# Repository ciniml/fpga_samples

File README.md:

# FPGA Samples

GOWIN LittleBeeなどの小規模FPGA向けのサンプルやライブラリ

## 内容

### rtl

SystemVerilogで記述したモジュール

### src/main/scala

Chisel3で記述したモジュール

### src/test/scala

Chisel3で記述したモジュールのテスト

## ライセンス

Boost Software License 1.0

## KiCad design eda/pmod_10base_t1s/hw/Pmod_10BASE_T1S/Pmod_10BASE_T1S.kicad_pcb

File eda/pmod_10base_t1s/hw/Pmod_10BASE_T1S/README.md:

# Pmod 10BASE-T1S (Rev. A)

IEEE 802.3cg 10BASE-T1S のバスに、**PHY チップを使わずに**つなぐ Pmod 基板。PCS / PMA / PLCA は FPGA のロジック
(`rtl/t1s_phy`) で実装し、基板には受動部品と、アナログスイッチ 1 個・CMC・ESD アレイだけを載せる。
送信は「RC + アナログスイッチ」と「直列インダクタ (Basic / Preferred 部品だけ)」の 2 通りを載せてあり、ハンダジャンパで選ぶ。
検討の経緯と規格の要件は [`../../README.md`](../../README.md)。KiCad 10、2 層。

状態: **設計のみ (未発注・実機未確認)**。

## 仕様

- 外形 20.32 × 44 mm (Pmod 1 スロット幅)、2 層 1.6 mm (B.Cu は GND ベタ)、角 1.27 mm 面取り。
- J1: Pmod 2x6 直角ヘッダ (`Conn_Pmod_Spec_B_Thin`)、上端。Digilent のピン 1 は部品面から見て右端。
- J2: 5.0 mm 2 ピンねじ端子 (KF301-5.0-2P、フットプリントは互換の MaiXu MX126)、下端。1 = BI_DA+ (シルク「+」)、2 = BI_DA−。
  DME は極性に依存しないので逆につないでも動く。挿入実装なので手はんだを既定にする (`jlc_files.py --with-tht` で JLC 実装に含める)。
- J3: 2.54 mm 3 ピン (線 +、線 −、GND、**未実装**)。プローブやジャンパ線用。
- JP1: 2 ピンヘッダ + ショートピン。**バスの両端のノードだけ**挿して 100 Ω のエンド終端を入れる。
- JP2 / JP3: 3 パッドのハンダジャンパ (TX+ / TX−)。送信経路の選択 (下の「送信経路の切り替え」)。
- 電源: Pmod VCC (3.3 V) のみ。PoDL 非対応 (給電されたバスにつながない)。

| J1 ピン | 信号 | 種類 | TP25K J6 (pmod0) |
|---|---|---|---|
| 1 / 7 | CMP_HP / CMP_HN (比較器 H: v > +th) | LVDS25 入力 | F5 / G5 |
| 2 / 8 | CMP_LP / CMP_LN (比較器 L: v > −th) | LVDS25 入力 | G7 / G8 |
| 3 | PWM_TH (しきい値) | LVCMOS33 出力 | H8 |
| 9 | TX_EN (TMUX1511 SEL1/SEL2、基板で 10 kΩ プルダウン。L 経路では常に Low) | LVCMOS33 出力 | H7 |
| 4 / 10 | TX_P / TX_N | LVCMOS33 出力 DRIVE=16 | H5 / J5 |

並びは `eda/pmod_100base_tx` と同じ (9 番だけ 2 本目の PWM から TX_EN に変更)。

## 回路

| Ref | 値 | 役割 |
|---|---|---|
| R1 / R2 | 100 Ω | 送信の直列抵抗 (FPGA 側、両経路で共通)。SW 経路はピン抵抗 + R1 + Ron + R5 ≈ 145 Ω/片側で、50 Ω (両端終端の並列) に約 1.0 Vpp。実測で合わせる |
| JP2 / JP3 | ハンダジャンパ 3 パッド | 中央 = R1 / R2 の出力。1-2 (出荷時、銅箔で短絡) = SW 経路、2-3 = L 経路 |
| C1 / C2 | 220 pF | SW 経路: 立ち上がりを約 10 ns (20〜80%) に鈍らせる。スイッチの FPGA 側にあるので、休止中はバスから見えない |
| U1 | TMUX1511 | SW 経路: 送信の切り離し (SW1/SW2、SEL = TX_EN)。Ron 2 Ω、COFF 最大 4 pF、電源断でも 3.6 V まで絶縁。SW3/SW4 は未使用 (GND) |
| R5 / R6 | 22 Ω | SW 経路: 送信の直列抵抗 (線路側) |
| L2 / L3 | 1 µH 0805 (Sunlord SDFL2012Q1R0KTF、50 mA) | L 経路: R1 / R2 と直列で立ち上がりを鈍らせ、TRX に直結。直列素子なので休止中に容量として見えない |
| R7 | 10 kΩ | TX_EN のプルダウン (FPGA の未コンフィグ時の弱プルアップでスイッチが入らないように) |
| R8 / R9 | 20 kΩ | TRX_P / TRX_N を VB にバイアス (比較器の VB 側の入力を兼ねる) |
| C4 / C5、R12 / R14 | 100 nF、20 kΩ | 比較器の VTH 側のタップ (AC 結合 + VTH へバイアス) |
| R10 / R11 / R13 / R15 | 1 kΩ | FPGA の各ピンとの直列抵抗 (ピン容量を高域で隠す、ESD 電流の制限) |
| R16 / R17 / C6 / C7 | 3.3 kΩ / 2 kΩ / 10 µF / 100 nF | VB = 1.245 V |
| R18 / R19 / C8 | 5.1 kΩ / 1 kΩ / 1 µF | PWM → VTH。th = VTH − VB = (D × 3.3 V − VB) × 0.164 = −204〜+337 mV |
| U2 | TPD4E02B04 | ESD (トランシーバ側、2 チャネル使用、フロースルー) |
| L1 | ACT1210L-201 (200 µH) | コモンモードチョーク。フットプリントはデータシートの推奨ランドから生成 (`gen_sch.py`) |
| C9 / C10 | 100 nF 50 V | DC 阻止 |
| R20 / R21 / C11 / R22 | 49.9 Ω ×2 / 100 nF / 100 kΩ | エンド終端 (JP1 で入/切) と静電気逃がし (OPEN Alliance の R1/R2/C3/R3) |
| R23 / R24 | 1.5 kΩ (**未実装**) | コモンモード終端 (ドロップノードの任意項目) |
| C12 / C13 / C3 | 10 µF / 100 nF / 100 nF | 3.3 V、U1 の電源 |

## 送信経路の切り替え

| | SW 経路 (JP2 / JP3 = 1-2、出荷時) | L 経路 (JP2 / JP3 = 2-3) |
|---|---|---|
| 回路 | 100 Ω → 220 pF → TMUX1511 → 22 Ω | 100 Ω → 1 µH → TRX 直結 |
| 振幅 (50 Ω) | 約 1.0 Vpp | 1.00〜1.13 Vpp (FPGA のピン抵抗 40〜20 Ω) |
| 立ち上がり (20〜80%、50 Ω‖15 pF) | 約 10 ns | 10.5〜11.8 ns |
| 休止中の high-Z | スイッチで切断 (電源断でも) | FPGA のトライステート。電源断時は DC 阻止の後ろで ±0.25 V しか振れないので FPGA の保護ダイオードはほぼ導通しない |
| 休止中の容量 | TMUX の COFF + 22 Ω | FPGA の TX ピン容量 (推定 5〜10 pF) を 100 Ω + 1 µH 越しに見る。5 pF なら全帯域で下限を満たす (40 MHz で 202 Ω、下限 159 Ω)。10 pF だと直列共振が 50 MHz に下がり、40 MHz で 152 Ω と下限をわずかに割る (`../../tools/calc.py`、要実測) |
| Extended 部品 | TMUX1511 | なし (L2 / L3 は Preferred) |
| FPGA の設定 | `d` = 0 (既定): TX_EN でスイッチ、TX ピンは常に駆動 | `d` = 1: TX_EN は常に Low、TX ピンは P ≠ N の間だけ駆動 (アイドルと PRE / POST はトライステート) |

- 切り替え: 1-2 の間の細い銅箔をカッターで切り、2-3 をハンダでつなぐ。戻すときは 2-3 のハンダを除いて 1-2 をつなぐ。
  L 経路では U1 は載っていてもよい (TX_EN が Low なのでオフ)。
- **発注は両方の経路を載せる構成を既定とする** (`fab/jlc` の BOM / CPL は U1・C1〜C3・R5 / R6 と L2 / L3 をすべて含む)。ジャンパだけで 2 方式を
  実測で比べられるため (TMUX1511 の LCSC 単体の在庫は 2026-11-20 に 0、11-21 に 1,863 個と変動する)。
  コスト (2026-11-21、JLC 少量単価、Extended 手数料 $3/種類): 両方載せると 5 枚で約 $17.1 (部品 $1.62/枚 + 手数料 $9)。
  SW 経路だけなら $16.6、L 経路だけ (U1 / C1〜C3 / R5 / R6 なし) なら $11.4 で、L 経路だけにして減るのは U1 の手数料 $3 と部品 約 $0.43/枚。
  大きく効くのは U2 (ESD) と L1 (CMC) で、手数料 $6 と部品 $0.89/枚 (ただし線路の保護をなくすことになる。L1 を外すには迂回パッドの追加が要る)。
- **SW 経路のまま L2 / L3 が載っていても問題ない** (ジャンパの 3 番が開いているので L は片側が浮く)。逆に L 経路で 1-2 の銅箔を
  切り忘れると、220 pF が L 越しにバスに見えて休止中の容量が規格を大きく超える。
- L 経路の値は ngspice の見積り (`tools/tx_lr.cir`)。FPGA の DRIVE 設定でピン抵抗が変わるので、振幅はオシロで確認する。

## 配線

- 自動配線 (circuitpnr、F.Cu / B.Cu)。ESD アレイの対向パッド (フロースルー) から CMC、CMC から DC 阻止コンデンサまでは
  `tools/gen_pcb.py` で手引き (自動配線が対向パッドの片側を取りこぼすため)。
- 12.5 MBd なので等長・差動インピーダンスは考慮していない。線路系のネット (LINE_*, CM_*, TRX_*) は幅 0.3 mm。

## 生成と製造データ

`tools/build.sh --regen` で回路図・基板を作り直し (gen_sch.py → gen_pcb.py → circuitpnr route / labels)、ERC / DRC
(回路図との一致を含む) のあと `fab/` にガーバー、ドリル、BOM、配置、回路図 PDF、画像を書く。`--regen` なしは今の KiCad ファイルから
製造データだけを出す。生成の流儀は Pmod_DVI / Pmod_GbE と同じ (Python)。

部品 (2026-11-20 照会): TMUX1511PWR は JLC 実装在庫 7,737 個 (LCSC 単体の在庫は 0、11-21 の再照会で 1,863 個)、ACT1210L-201 は 2.6 万個、TPD4E02B04 は 7.2 万個。
2026-11-21 照会: 抵抗は全部 Basic (22 Ω C25092、3.3 kΩ C25890、2 kΩ C4109、5.1 kΩ C25905 に変更)、1 µH の C1042 は Preferred (在庫 6 万個)。
Extended は U1 (TMUX1511)・U2 (ESD)・L1 (CMC)・J2 (ねじ端子、既定で手はんだ) の 4 種類。
`tools/lcsc_order.py N` で手はんだ用の LCSC 購入リスト (`fab/lcsc/`、5 枚分を 2026-11-21 に再生成。C14663 (100 nF 50 V 0603) と C1042 (1 µH) は LCSC 単体の在庫が 0 なので、手はんだ分は同等品を探す)。

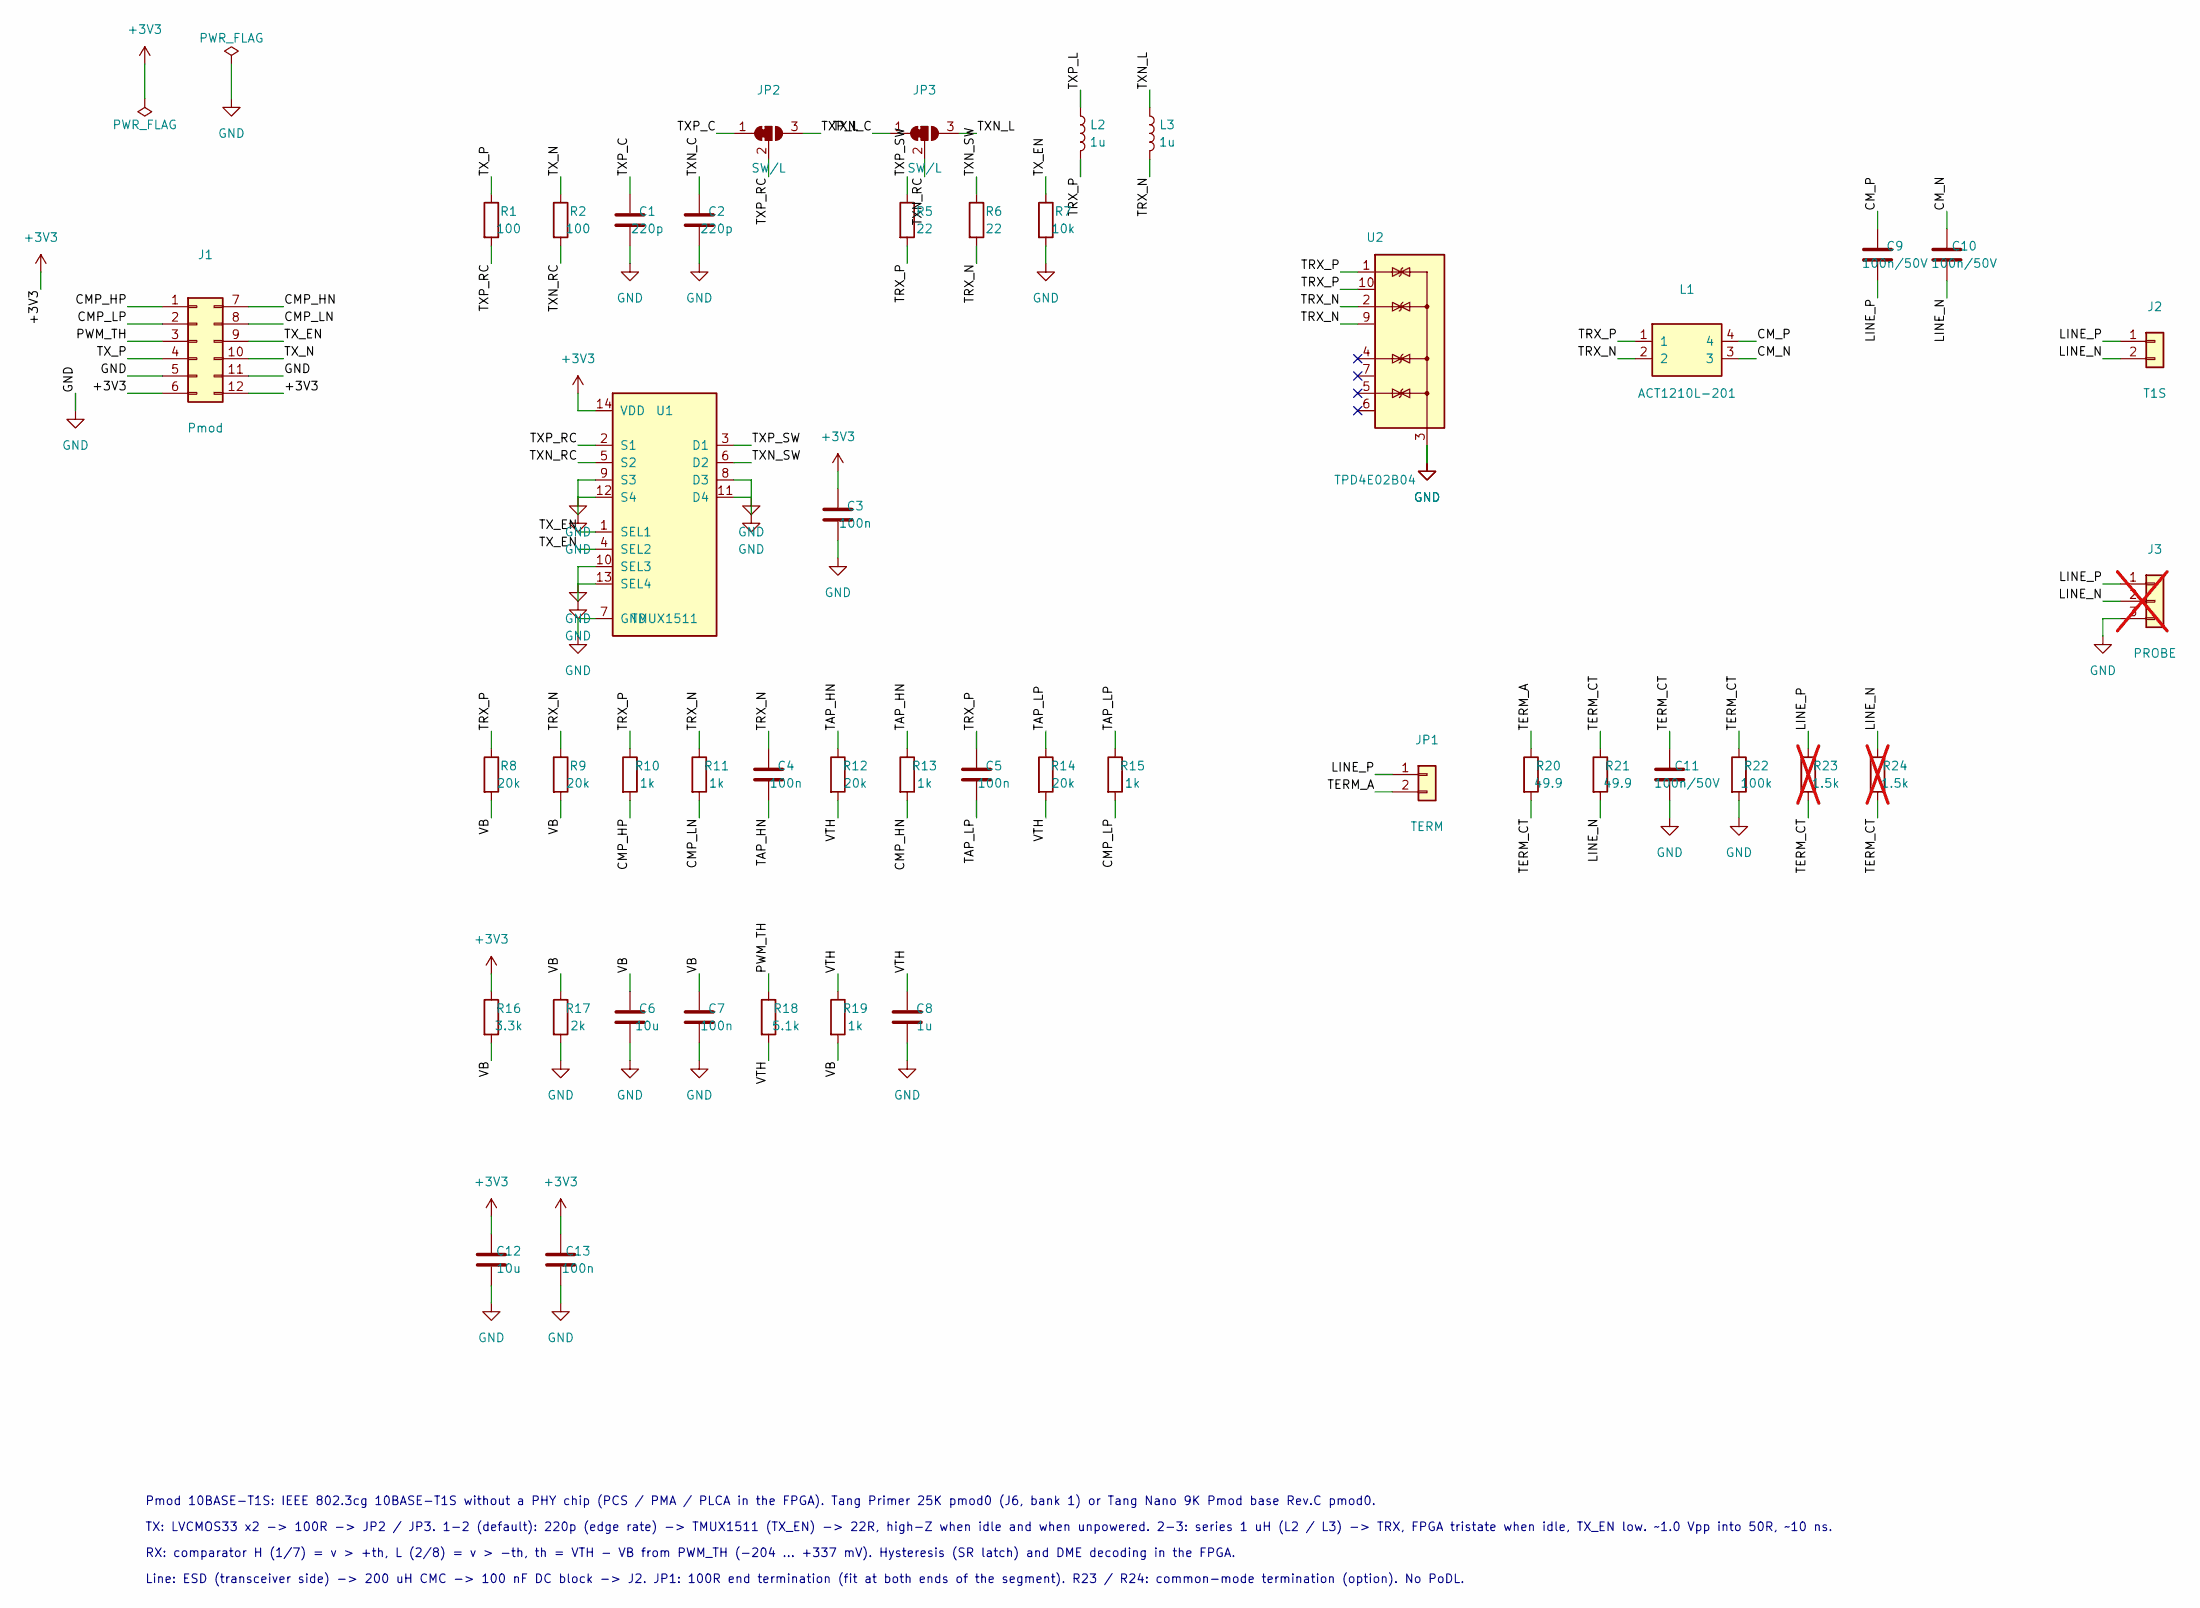
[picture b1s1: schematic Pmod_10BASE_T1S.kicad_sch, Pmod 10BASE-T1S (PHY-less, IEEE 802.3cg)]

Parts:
C1, C2: 220p; C_0402_1005Metric; MPN FH 0402B221K500NT; LCSC C1530
C3, C4, C5, C7, C13: 100n; C_0402_1005Metric; MPN Samsung CL05B104KO5NNNC; LCSC C1525
C6, C12: 10u; C_0603_1608Metric; MPN Samsung CL10A106KP8NNNC; LCSC C19702
C8: 1u; C_0402_1005Metric; MPN Samsung CL05A105KA5NQNC; LCSC C52923
C9, C10, C11: 100n/50V; C_0603_1608Metric; MPN YAGEO CC0603KRX7R9BB104; LCSC C14663
J1: Pmod; Conn_Pmod_Spec_B_Thin
J2: T1S; TerminalBlock_MaiXu_MX126-5.0-02P_1x02_P5.00mm; MPN Cixi Kefa KF301-5.0-2P; LCSC C474881
J3: PROBE; PinHeader_1x03_P2.54mm_Vertical; not fitted
JP1: TERM; PinHeader_1x02_P2.54mm_Vertical
JP2, JP3: SW/L; SolderJumper-3_P1.3mm_Bridged12_RoundedPad1.0x1.5mm_NumberL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
L1: ACT1210L-201; L_CommonModeChoke_TDK_ACT1210; MPN TDK ACT1210L-201-2P-TL00; LCSC C131444
L2, L3: 1u; L_0805_2012Metric; MPN Sunlord SDFL2012Q1R0KTF; LCSC C1042
R1, R2: 100; R_0402_1005Metric; MPN UNI-ROYAL 0402WGF1000TCE; LCSC C25076
R5, R6: 22; R_0402_1005Metric; MPN UNI-ROYAL 0402WGF220JTCE; LCSC C25092
R7: 10k; R_0402_1005Metric; MPN UNI-ROYAL 0402WGF1002TCE; LCSC C25744
R8, R9, R12, R14: 20k; R_0402_1005Metric; MPN UNI-ROYAL 0402WGF2002TCE; LCSC C25765
R10, R11, R13, R15, R19: 1k; R_0402_1005Metric; MPN UNI-ROYAL 0402WGF1001TCE; LCSC C11702
R16: 3.3k; R_0402_1005Metric; MPN UNI-ROYAL 0402WGF3301TCE; LCSC C25890
R17: 2k; R_0402_1005Metric; MPN UNI-ROYAL 0402WGF2001TCE; LCSC C4109
R18: 5.1k; R_0402_1005Metric; MPN UNI-ROYAL 0402WGF5101TCE; LCSC C25905
R20, R21: 49.9; R_0402_1005Metric; MPN UNI-ROYAL 0402WGF499JTCE; LCSC C25120
R22: 100k; R_0402_1005Metric; MPN UNI-ROYAL 0402WGF1003TCE; LCSC C25741
R23, R24: 1.5k; R_0603_1608Metric; MPN UNI-ROYAL 0603WAF1501T5E; LCSC C22843; not fitted
U1: TMUX1511; TSSOP-14_4.4x5mm_P0.65mm; MPN TI TMUX1511PWR; LCSC C2866750
U2: TPD4E02B04; USON-10_2.5x1.0mm_P0.5mm; MPN TI TPD4E02B04DQAR; LCSC C106794

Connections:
+3V3: C3.1, C12.1, C13.1, J1.6, J1.12, R16.1, U1.14 (VDD)
/CMP_HN: J1.7, R13.2
/CMP_HP: J1.1, R10.2
/CMP_LN: J1.8, R11.2
/CMP_LP: J1.2, R15.2
/CM_N: C10.1, L1.3
/CM_P: C9.1, L1.4
/LINE_N: C10.2, J2.2, J3.2, R21.2, R24.1
/LINE_P: C9.2, J2.1, J3.1, JP1.1, R23.1
/PWM_TH: J1.3, R18.1
/TAP_HN: C4.2, R12.1, R13.1
/TAP_LP: C5.2, R14.1, R15.1
/TERM_A: JP1.2, R20.1
/TERM_CT: C11.1, R20.2, R21.1, R22.1, R23.2, R24.2
/TRX_N: C4.1, L1.2, L3.2, R6.2, R9.1, R11.1, U2.2 (IO2), U2.9 (NC)
/TRX_P: C5.1, L1.1, L2.2, R5.2, R8.1, R10.1, U2.1 (IO1), U2.10 (NC)
/TXN_C: C2.1, JP3.1 (A)
/TXN_L: JP3.3 (B), L3.1
/TXN_RC: JP3.2 (C), R2.2, U1.5 (S2)
/TXN_SW: R6.1, U1.6 (D2)
/TXP_C: C1.1, JP2.1 (A)
/TXP_L: JP2.3 (B), L2.1
/TXP_RC: JP2.2 (C), R1.2, U1.2 (S1)
/TXP_SW: R5.1, U1.3 (D1)
/TX_EN: J1.9, R7.1, U1.1 (SEL1), U1.4 (SEL2)
/TX_N: J1.10, R2.1
/TX_P: J1.4, R1.1
/VB: C6.1, C7.1, R8.2, R9.2, R16.2, R17.1, R19.2
/VTH: C8.1, R12.2, R14.2, R18.2, R19.1
GND: C1.2, C2.2, C3.2, C6.2, C7.2, C8.2, C11.2, C12.2, C13.2, J1.5, J1.11, J3.3, R7.2, R17.2, R22.2, U1.7 (GND), U1.8 (D3), U1.9 (S3), U1.10 (SEL3), U1.11 (D4), U1.12 (S4), U1.13 (SEL4), U2.3 (G), U2.8 (G)

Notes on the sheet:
Pmod 10BASE-T1S: IEEE 802.3cg 10BASE-T1S without a PHY chip (PCS / PMA / PLCA in the FPGA). Tang Primer 25K pmod0 (J6, bank 1) or Tang Nano 9K Pmod base Rev.C pmod0.
TX: LVCMOS33 x2 -> 100R -> JP2 / JP3. 1-2 (default): 220p (edge rate) -> TMUX1511 (TX_EN) -> 22R, high-Z when idle and when unpowered. 2-3: series 1 uH (L2 / L3) -> TRX, FPGA tristate when idle, TX_EN low. ~1.0 Vpp into 50R, ~10 ns.
RX: comparator H (1/7) = v > +th, L (2/8) = v > -th, th = VTH - VB from PWM_TH (-204 ... +337 mV). Hysteresis (SR latch) and DME decoding in the FPGA.
Line: ESD (transceiver side) -> 200 uH CMC -> 100 nF DC block -> J2. JP1: 100R end termination (fit at both ends of the segment). R23 / R24: common-mode termination (option). No PoDL.

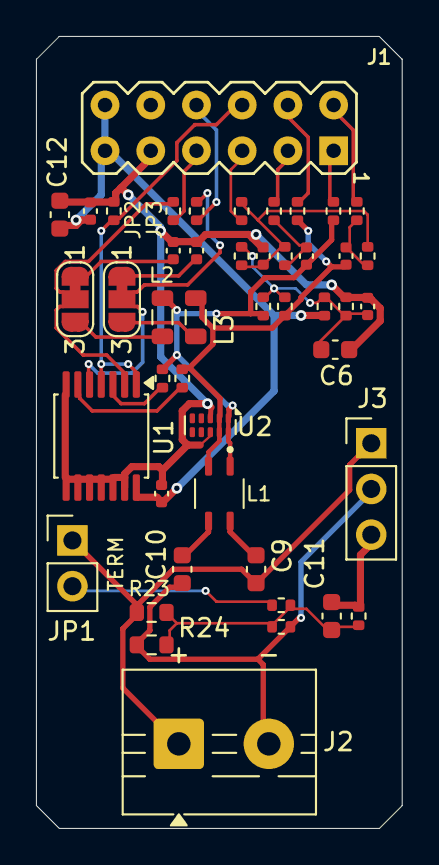
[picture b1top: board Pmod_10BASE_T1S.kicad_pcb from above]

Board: 2 copper layers, 20.3 x 44.0 mm, 47 parts (1 on the bottom side), 30 nets.

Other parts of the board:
LOGO1: Logo_Open_Hardware_Small; logo

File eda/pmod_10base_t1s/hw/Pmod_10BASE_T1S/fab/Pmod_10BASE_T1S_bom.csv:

"Reference","Value","Footprint","QUANTITY","LCSC","MPN","Description"
"C1,C2","220p","Capacitor_SMD:C_0402_1005Metric","2","C1530","FH 0402B221K500NT","220 pF 50 V X7R 0402 (TX+ edge rate ~10 ns 20-80 %, hidden by U1 when idle; JP2 1-2),220 pF 50 V X7R 0402 (TX- edge rate; JP3 1-2)"
"C3-C5,C7,C13","100n","Capacitor_SMD:C_0402_1005Metric","5","C1525","Samsung CL05B104KO5NNNC","100 nF 16 V X7R 0402 (Pmod VCC),100 nF 16 V X7R 0402 (U1 VDD),100 nF 16 V X7R 0402 (VB),100 nF 16 V X7R 0402 (comparator H - tap, AC coupled),100 nF 16 V X7R 0402 (comparator L + tap, AC coupled)"
"C6,C12","10u","Capacitor_SMD:C_0603_1608Metric","2","C19702","Samsung CL10A106KP8NNNC","10 uF 10 V X5R 0603 (Pmod VCC),10 uF 10 V X5R 0603 (VB)"
"C8","1u","Capacitor_SMD:C_0402_1005Metric","1","C52923","Samsung CL05A105KA5NQNC","1 uF 25 V X5R 0402 (VTH, tau 0.85 ms)"
"C9-C11","100n/50V","Capacitor_SMD:C_0603_1608Metric","3","C14663","YAGEO CC0603KRX7R9BB104","100 nF 50 V X7R 0603 (DC block +),100 nF 50 V X7R 0603 (DC block -),100 nF 50 V X7R 0603 (termination centre, OPEN Alliance C3)"
"J1","Pmod","local:Conn_Pmod_Spec_B_Thin","1","","","Pmod 2x6 right angle (Digilent Pmod Type 1A / spec B)"
"J2","T1S","TerminalBlock:TerminalBlock_MaiXu_MX126-5.0-02P_1x02_P5.00mm","1","C474881","Cixi Kefa KF301-5.0-2P","5.0 mm 2-pin screw terminal (KF301-5.0-2P): 1 = BI_DA+, 2 = BI_DA-"
"JP1","TERM","Connector_PinHeader_2.54mm:PinHeader_1x02_P2.54mm_Vertical","1","","","2-pin header + shunt: fit to terminate (100R) at the ends of a mixing segment"
"L1","ACT1210L-201","local:L_CommonModeChoke_TDK_ACT1210","1","C131444","TDK ACT1210L-201-2P-TL00","TDK ACT1210L-201-2P-TL00 common mode choke, 200 uH, 2 lines, 3.2x2.5 mm (windings 1-4, 2-3)"
"L2,L3","1u","Inductor_SMD:L_0805_2012Metric","2","C1042","Sunlord SDFL2012Q1R0KTF","1 uH 0805 multilayer (TX- series-L path),1 uH 0805 multilayer, 50 mA (TX+ series-L path, edge rate with R1)"
"R1,R2","100","Resistor_SMD:R_0402_1005Metric","2","C25076","UNI-ROYAL 0402WGF1000TCE","100R 1% 0402 (TX+ series; tune R1 / R2 for 1.0 Vpp),100R 1% 0402 (TX- series)"
"R5,R6","22","Resistor_SMD:R_0402_1005Metric","2","C25092","UNI-ROYAL 0402WGF220JTCE","22R 1% 0402 (TX+ series, line side of the switch),22R 1% 0402 (TX- series)"
"R7","10k","Resistor_SMD:R_0402_1005Metric","1","C25744","UNI-ROYAL 0402WGF1002TCE","10k 1% 0402 (TX_EN pull-down: switch off while the FPGA is unconfigured)"
"R8,R9,R12,R14","20k","Resistor_SMD:R_0402_1005Metric","4","C25765","UNI-ROYAL 0402WGF2002TCE","20k 1% 0402 (TRX+ bias to VB),20k 1% 0402 (TRX- bias to VB),20k 1% 0402 (comparator H - tap bias to VTH),20k 1% 0402 (comparator L + tap bias to VTH)"
"R10,R11,R13,R15,R19","1k","Resistor_SMD:R_0402_1005Metric","5","C11702","UNI-ROYAL 0402WGF1001TCE","1k 1% 0402 (PWM filter to VB),1k 1% 0402 (comparator H +: VB + v+),1k 1% 0402 (comparator H -: VTH + v-),1k 1% 0402 (comparator L +: VTH + v+),1k 1% 0402 (comparator L -: VB + v-)"
"R16","3.3k","Resistor_SMD:R_0402_1005Metric","1","C25890","UNI-ROYAL 0402WGF3301TCE","3.3k 1% 0402 (VB = 1.245 V with R17)"
"R17","2k","Resistor_SMD:R_0402_1005Metric","1","C4109","UNI-ROYAL 0402WGF2001TCE","2k 1% 0402 (VB divider)"
"R18","5.1k","Resistor_SMD:R_0402_1005Metric","1","C25905","UNI-ROYAL 0402WGF5101TCE","5.1k 1% 0402 (PWM filter: th = (D x 3.3 V - VB) x 0.164)"
"R20,R21","49.9","Resistor_SMD:R_0402_1005Metric","2","C25120","UNI-ROYAL 0402WGF499JTCE","49.9R 1% 0402 (end termination half)"
"R22","100k","Resistor_SMD:R_0402_1005Metric","1","C25741","UNI-ROYAL 0402WGF1003TCE","100k 1% 0402 (static discharge, OPEN Alliance R3)"
"U1","TMUX1511","Package_SO:TSSOP-14_4.4x5mm_P0.65mm","1","C2866750","TI TMUX1511PWR","TI TMUX1511 4-channel SPST switch, 2 Ohm, 3.3 pF, powered-off protected, 1.8 V logic, TSSOP-14"
"U2","TPD4E02B04","Package_SON:USON-10_2.5x1.0mm_P0.5mm","1","C106794","TI TPD4E02B04DQAR","4-channel ESD protection, 0.25 pF, USON-10 flow-through (2 channels used)"

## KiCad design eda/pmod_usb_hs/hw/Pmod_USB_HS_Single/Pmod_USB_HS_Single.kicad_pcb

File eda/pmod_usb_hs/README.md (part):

# Pmod USB 2.0 HS デバイス基板

`rtl/usb` の PHY コア (UTMI/ULPI、HS/FS/LS) を Tang Primer 25K などの Pmod で実機評価するための基板。

## 現状 (2026-11-15)

実際に作ったのは **1 Pmod 版の [Pmod USB HS Single](hw/Pmod_USB_HS_Single/README.md)** (Single LVDS、D- 比較器なしの 7 本 + VBUS 検出)。
この README の §1 以降は、最初に検討した **2 ポート版 (Dual LVDS)** の設計検討で、2 ポート版の回路図と基板はこのリポジトリにない。

| 対象 | 状態 |
|---|---|
| Pmod USB HS Single (`hw/Pmod_USB_HS_Single`) | JLCPCB に発注 (発注番号 Y118)、組み立て済み。Tang Primer 25K の pmod1 で **HS の列挙とバルク転送を実機確認** (2026-11-09、片方向 21.7 MB/s で 4.4 GB 不一致 0)。FS での通信は未確認。手順と結果は [hw/Pmod_USB_HS_Single/README.md](hw/Pmod_USB_HS_Single/README.md) |
| 2 ポート版 (TN710 Dual LVDS、本 README §1〜) | 設計検討のみ。2 コネクタ構成の Pmod USB 基板での `rtl/usb` の HS 実機評価は [`eda/usb_device/README.md`](../usb_device/README.md) にある |
| PHY ラッパ | 1 Pmod 版: `rtl/usb/gowin/usb_phy_gowin_sl.v` (`CMP1=1`、SLogic16U3 と共用)。2 コネクタ版: `rtl/usb/gowin/usb_phy_gowin_p.v` |

ドキュメント:

- [SINGLE_PMOD.md](SINGLE_PMOD.md): 1 Pmod 版 (Single LVDS、9 本 → 7 本) の設計検討。
- [hw/Pmod_USB_HS_Single/README.md](hw/Pmod_USB_HS_Single/README.md): 1 Pmod 版の基板 (KiCad、製造データ、部品、実機確認の結果)。
- [`eda/usb_device`](../usb_device/README.md): Tang Primer 25K のデザイン。1 Pmod 版は `make USB_SL=1`。
- [SURVEY.md](SURVEY.md): `rtl/usb` を実機で動かすための調査記録 (2026-08-25)。
- [FROM_EXTEASYCDR.md](FROM_EXTEASYCDR.md): ExtEasyCDR の回路図から 2 ポート版を起こすための引き継ぎ情報。

## 2 ポート版 (Dual LVDS) の設計検討

Gowin USB 2.0 SoftPHY IP の **Dual LVDS モード**
(IPUG781 §3.2 図 3-3) と **TN710 (Gowin USB 2.0 SoftPHY Device Peripheral Circuit Design
Application Note) の USB2.0-RC 回路**をベースに、Pmod 2 ポート分の I/O に収めた。コネクタは USB Type-C レセプタクル (USB 2.0 専用、SS レーンなし)。

状態: **机上検討のみ** (この構成の回路図/基板は作っていない。実際に作ったのは上記の 1 Pmod 版)。

## 1. 要求と方針

| 項目 | 内容 |
|---|---|
| 速度 | HS 480Mbps (目標) / FS 12Mbps (必ず動かす) / LS は非対象 |
| 役割 | デバイス (UFP) のみ。ホスト/OTG なし。VBUS は電源に使わない |
| 回路 | **Gowin TN710 の USB2.0-RC 回路をそのまま採用** (R1〜R9, C1 の定数はデバイスファミリ別) |
| FPGA 側 I/F | `rtl/usb/usb_phy.veryl` (`UsbPhy`) のシリアル側: `i_rx_dd` (差動レシーバ)、`i_rx_dp/dn` (単端コンパレータ)、`o_tx_dp/dn`, `o_tx_oe`, `o_pullup_dp_en`, `o_term_dp/dn_en`。ラッパは `rtl/usb/gowin/usb_phy_gowin.v` |
| Pmod | 2 ポート占有 (既存 `Pmod_DisplayPort` と同じ `Conn_Pmod_Spec_B_Thin` ×2 横並び)。3.3V バンク |
| コネクタ | Molex 105450-0101 (USB2.0 専用 16pin Type-C、`ExtEasyCDR` と同じ) |

TN710 の必要 I/O は 11 本 (差動対 4 + 単端 3)。1 Pmod (8 I/O、差動対 4) には
収まらないため 2 ポートにする。VBUS 検出を 1 本追加して 12 本。

## 2. 回路 (TN710 USB2.0-RC 準拠)

### 2.1 ブロック図

```
 Type-C (USB2.0 only)                USB2.0-RC (Pmod 基板)                  FPGA (Pmod 経由)
 VBUS (A4,A9,B4,B9) ──┬─ 100k/22k ─── VBUS_DET ───────────────────────── LVCMOS33 in
                      └─ 1uF
 CC1 ── 5.1k ── GND, CC2 ── 5.1k ── GND   (UFP: Rd)

 D+ (A6,B6) ─┬─ ESD ─┬───────────────────────── R4 0Ω ── USB_RX_D+  ┐ TRUE LVDS 入力対 (HS データ)
 D- (A7,B7) ─┼─ ESD ─┼───────────────────────── R5 0Ω ── USB_RX_D-  ┘
   90Ω 差動   │       ├── R6 ── USB_TX_D+                            ┐ LVCMOS33D 出力対 (直列 R6/R7)
              │       ├── R7 ── USB_TX_D-                            ┘
              │       ├── R1 1.5k ── USB_PULLUP_EN                     LVCMOS33 out (D+ のみ)
              │       ├── R2 ── USB_TERM_RXDP                          LVCMOS33 out (L 駆動 = 45Ω 終端)
              │       ├── R3 ── USB_TERM_RXDN                          LVCMOS33 out
              │       ├────────── USB_RXDP_D+ ┐ LVDS25 入力対 (単端 D+ コンパレータ)
              │       │   VREF ── USB_RXDP_D- ┘
              │       └────────── USB_RXDN_D+ ┐ LVDS25 入力対 (単端 D- コンパレータ)
              │           VREF ── USB_RXDN_D- ┘
 VREF = 3.3V × R9/(R8+R9) ≈ 130mV  (R8 1.8k, R9 75Ω, C1 1uF)
```

### 2.2 定数 (TN710 表)

| 部品 | LittleBee (Tang Nano 9K) | Arora (Primer 20K) | Arora-V (Tang Primer 25K) | 役割 |
|---|---|---|---|---|
| R1 | 1.5k | 1.5k | 1.5k | D+ プルアップ |
| R2, R3 | 0Ω | 0Ω | 36Ω | HS 終端 (ピン出力インピーダンス + R = 45Ω) |
| R4, R5 | 0Ω | 0Ω | 0Ω | 差動 RX 直結 |
| R6, R7 | 42Ω | 42Ω | 100Ω | TX 直列 (HS 400mV 振幅はピン DRIVE 設定と合わせて決まる) |
| R8 / R9 | 1.8k / 75Ω | 1.8k / 56Ω | 1.8k / 75Ω | VREF (≈130mV / ≈100mV / ≈130mV) |
| C1 | 1uF | 1uF | 1uF | VREF バイパス |

抵抗 1%・容量 20%、0402。**RC 部品は FPGA 側に寄せて配置** (TN710: "as close to FPGA as possible") —
Pmod 基板ではヘッダ直近に置く。

### 2.3 動作の割り当て (RTL 側)

- **HS データ**: 差動レシーバ `USB_RX_D+/-` → `i_rx_dd`。HS アイドル (SE0) は単端コンパレータ両方 L で検出 (スケルチ代用)
- **FS / チャープ / LineState**: 単端コンパレータ `USB_RXDP/RXDN` → `i_rx_dp/dn`。閾値 130mV は HS 0/400mV・チャープ 0/800mV・FS 0/3.3V のいずれにも有効
- **TX**: 1 対で FS/HS 共用。HS 振幅 400mV は「3.3V 出力 → (ピン出力インピーダンス + R6) → 22.5Ω」で作るため、
  IPUG781 の DRIVE 指定 (GW1N: DRIVE=8、GW2A: DRIVE=4、Arora-V: DRIVE=8) を守る。FS では同じ経路で 3.3V レベルを出す
- **チャープ K**: `OpMode=RAW` で TX 対から K (D- H / D+ L) を出す。FS プルアップは有効のまま
- **終端**: `o_term_dp/dn_en` = 1 のときピンを L 駆動 (それ以外は Z)。`o_pullup_dp_en` は H/Z

これらは `rtl/usb/gowin/usb_phy_gowin.v` (TLVDS_IBUF ×3 + IDES8 ×3 + OSER8 ×2 + TBUF ×2) で実装済み (未検証)。
差動 TX は TN710 では LVCMOS33D の 1 対だが、FS の SE0 (両線 L) を出す必要があるため
本ラッパでは 2 本の単端トライステートパッドとして扱う (レベルは同じ)。

### 2.4 保護・その他

- ESD: TPD2E001DRLR (TN710 リファレンス) または USBLC6-2SC6。線路容量 ~1pF 級
- Type-C: CC1/CC2 に 5.1kΩ (Rd)。これがないとホストが VBUS を出さず列挙されない
- VBUS: 100k/22k で 5V → 0.9V に落とし LVCMOS33 入力へ (接続検出、任意)。VBUS は Pmod に供給しない

## 3. Pmod ピン割り当て

TN710 の制約:
- 差動信号 (`USB_RX_D+/-`, `USB_RXDP`, `USB_RXDN`, `USB_TX_D+/-`) は **TRUE LVDS ピン**に置く
- LittleBee/Arora では `USB_RX_D+/-` の **隣接する下位番号の差動対が存在し未使用**であること (例: IOB13A/B を使うなら IOB12A/B を空ける)
- Arora-V 以外は全信号を同一バンクに置く

Pmod の上下段 (1/7, 2/8, 3/9, 4/10) は差動対として使える実績あり
(25K pmod2 の G11/G10、Nano 9K pmod0 の 26/25 (IOB8 真性ペア) を `easycdr_trace` で 1Gbps に使用)。

| Pmod A | 信号 | 種別 | Pmod B | 信号 | 種別 |
|---|---|---|---|---|---|
| 1 / 7 | USB_RX_D+ / D- | TRUE LVDS in | 1 / 7 | USB_TX_D+ / D- | LVCMOS33(D) out, R6/R7 |
| 2 / 8 | USB_RXDP_D+ (D+) / D- (VREF) | LVDS25 in | 2 | USB_PULLUP_EN | LVCMOS33 out, R1 |
| 3 / 9 | USB_RXDN_D+ (D-) / D- (VREF) | LVDS25 in | 3 | VBUS_DET | LVCMOS33 in |
| 4 / 10 | USB_TERM_RXDP / RXDN | LVCMOS33 out, R2/R3 | 4, 8, 9, 10 | (予備) | |
| 5,11 / 6,12 | GND / 3.3V | | 5,11 / 6,12 | GND / 3.3V | |

FPGA ピン (targets/*/pmod_ports.csv より):

| 信号 | Tang Primer 25K (A=pmod2, B=pmod1) | Tang Nano 9K (A=pmod0, B=pmod1) |
|---|---|---|
| USB_RX_D+ / D- | G11 / G10 | 28 / 27 (※1) |
| USB_RXDP_D+ / D- | D11 / D10 | 26 / 25 (IOB8 真性ペア) |
| USB_RXDN_D+ / D- | B11 / B10 | 39 / 36 (※1) |
| USB_TERM_RXDP / RXDN | C11 / C10 | 37 / 38 |
| USB_TX_D+ / D- | A11 / A10 | 42 / 41 (※1) |
| USB_PULLUP_EN | E11 | 35 |
| VBUS_DET | K11 | 34 |

※1 Nano 9K は 26/25 以外のペアが TRUE LVDS か未確認。また「隣接下位番号ペアを空ける」
制約を Pmod 配線で満たせるかは Nano 9K 回路図 (IOB 番号) で確認が必要。満たせない場合は
`USB_RX_D+/-` を 26/25 に移し、単端側を他ペアに振り替える。25K (Arora-V) にはこの制約がない。

### 3.1 Tang Primer 20K (GW2A-18, Arora) を加える場合

- 定数は LittleBee と **R9 のみ**異なる (56Ω → VREF ≈ 100mV)。R2/R3 = 0Ω、R6/R7 = 42Ω は共通。
  R9 を 0Ω ジャンパで 75Ω/56Ω 切替にすれば LittleBee/Arora は同一実装、Arora-V は R2/R3/R6/R7 も差し替え
- IO 制約: TX `DRIVE=4` (IPUG781 GW2A)、終端 `DRIVE=16`。ピン配置制約 (隣接下位番号ペア未使用・同一バンク) は
  LittleBee と同じ。GW2A-18 は **C8 なので C7 以上の条件を満たす** (Nano 9K の C6 と違い公式条件内)
- Pmod (dock 側 4 ポート、`targets/tangprimer20k/pmod_ports.csv`): pmod0 = P6/R8/P8/T9 + T6/T7/T8/P9 など。
  上下段が TRUE LVDS 対になっているかは PG256 ピン表で**未確認** (`easycdr_trace` の 20K 移植も未実施で実績なし)。
  対になっていなければ差動 4 対を確保できる Pmod の組を選び直す必要がある

## 4. FPGA 側の制約とラッパ

`rtl/usb/gowin/usb_phy_gowin.v` を使う。制約例 (25K, Arora-V。IPUG781 §3.2 の属性に準拠):

```
IO_LOC  "usb_rx_dp_i"  G11;  IO_LOC "usb_rx_dn_i"  G10;   // TRUE LVDS 対
IO_PORT "usb_rx_dp_i"  IO_TYPE=LVDS25 PULL_MODE=NONE DIFF_RESISTOR=OFF;
IO_LOC  "usb_rxdp_p_i" D11;  IO_LOC "usb_rxdp_n_i" D10;
IO_PORT "usb_rxdp_p_i" IO_TYPE=LVDS25 PULL_MODE=NONE DIFF_RESISTOR=OFF;
IO_LOC  "usb_rxdn_p_i" B11;  IO_LOC "usb_rxdn_n_i" B10;
IO_PORT "usb_rxdn_p_i" IO_TYPE=LVDS25 PULL_MODE=NONE DIFF_RESISTOR=OFF;
IO_LOC  "usb_tx_dp_o"  A11;  IO_LOC "usb_tx_dn_o"  A10;
IO_PORT "usb_tx_dp_o"  IO_TYPE=LVCMOS33 DRIVE=8 PULL_MODE=NONE;    // GW1N: DRIVE=8, GW2A: DRIVE=4
IO_PORT "usb_tx_dn_o"  IO_TYPE=LVCMOS33 DRIVE=8 PULL_MODE=NONE;
IO_LOC  "usb_term_dp_o" C11; IO_LOC "usb_term_dn_o" C10;
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
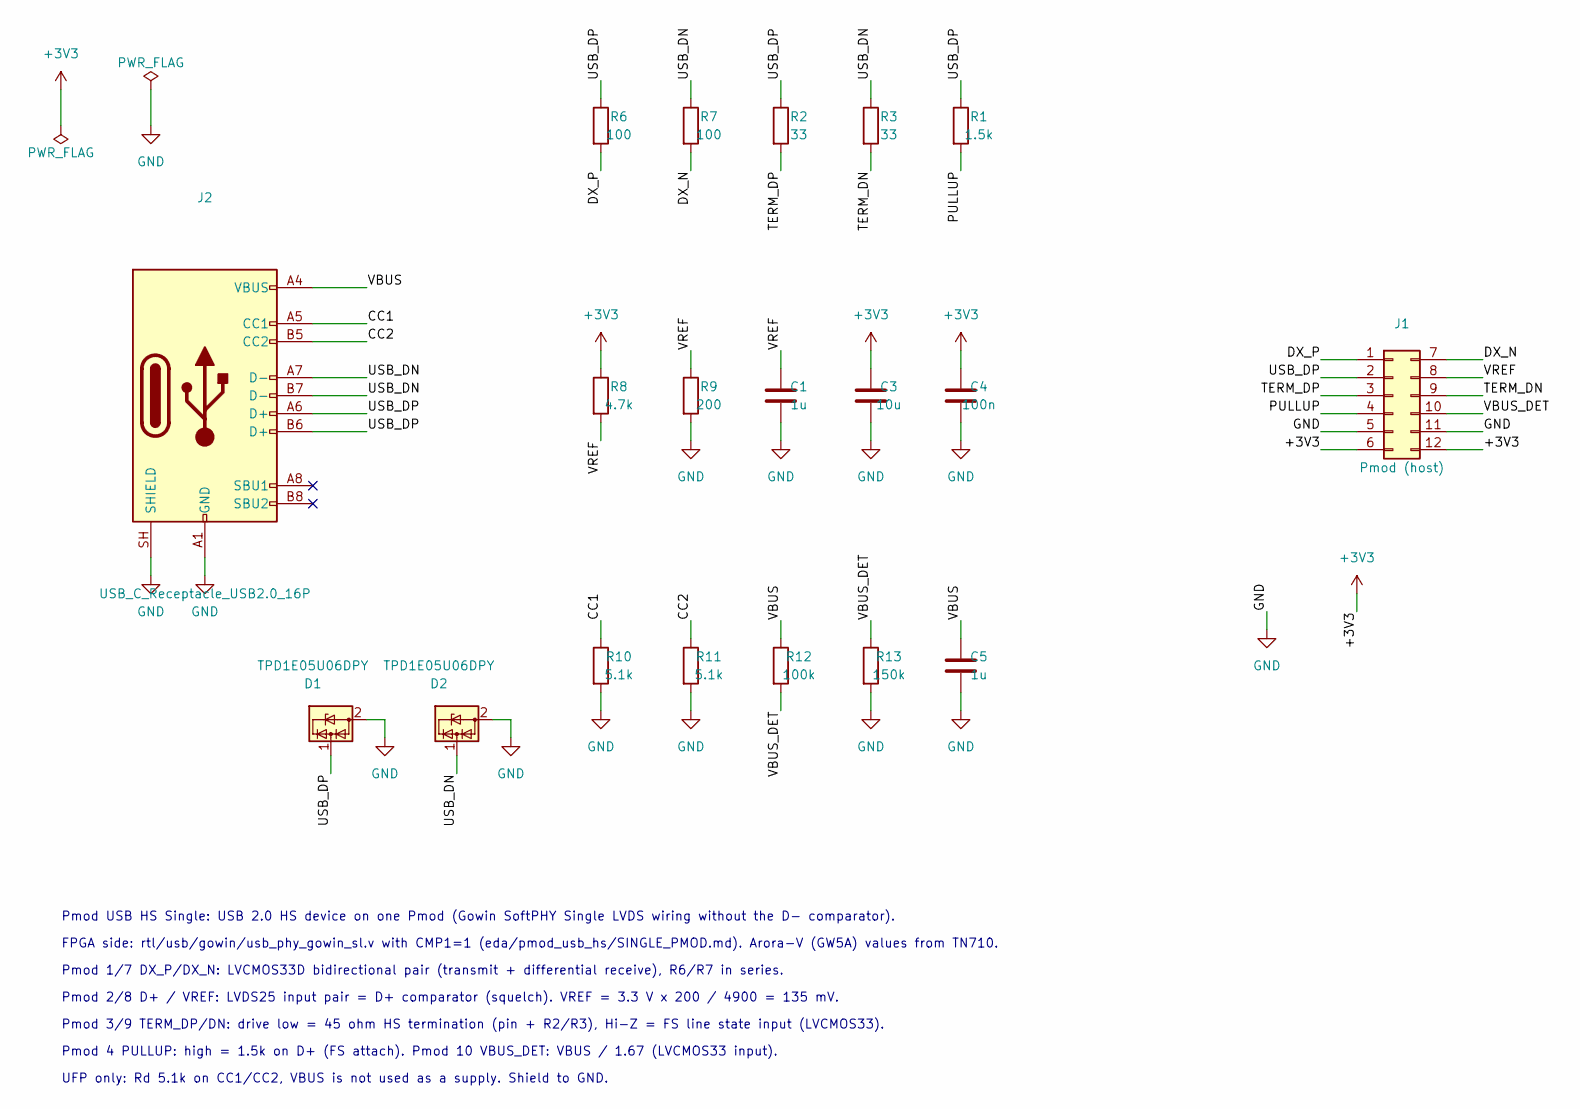
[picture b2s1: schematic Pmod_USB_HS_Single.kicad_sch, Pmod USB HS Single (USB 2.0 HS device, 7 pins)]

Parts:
C1, C5: 1u; C_0402_1005Metric; MPN Samsung CL05A105KA5NQNC; LCSC C52923
C3: 10u; C_0603_1608Metric; MPN Samsung CL10A106KP8NNNC; LCSC C19702
C4: 100n; C_0402_1005Metric; MPN Samsung CL05B104KB54PNC; LCSC C307331
D1, D2: TPD1E05U06DPY; Texas_DPY0002A_0.6x1mm_P0.65mm; MPN TI TPD1E05U06DPYR; LCSC C436349
J1: Pmod (host); Conn_Pmod_Spec_B_Thin
J2: USB_C_Receptacle_USB2.0_16P; USB_C_Receptacle_HRO_TYPE-C-31-M-12; MPN HRO TYPE-C-31-M-12; LCSC C165948
R1: 1.5k; R_0402_1005Metric; MPN UNI-ROYAL 0402WGF1501TCE; LCSC C25867
R2, R3: 33; R_0402_1005Metric; MPN UNI-ROYAL 0402WGF330JTCE; LCSC C25105
R6, R7: 100; R_0402_1005Metric; MPN UNI-ROYAL 0402WGF1000TCE; LCSC C25076
R8: 4.7k; R_0402_1005Metric; MPN UNI-ROYAL 0402WGF4701TCE; LCSC C25900
R9: 200; R_0402_1005Metric; MPN UNI-ROYAL 0402WGF2000TCE; LCSC C25087
R10, R11: 5.1k; R_0402_1005Metric; MPN UNI-ROYAL 0402WGF5101TCE; LCSC C25905
R12: 100k; R_0402_1005Metric; MPN UNI-ROYAL 0402WGF1003TCE; LCSC C25741
R13: 150k; R_0402_1005Metric; MPN UNI-ROYAL 0402WGF1503TCE; LCSC C25755

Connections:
+3V3: C3.1, C4.1, J1.6, J1.12, R8.1
/CC1: J2.A5 (CC1), R10.1
/CC2: J2.B5 (CC2), R11.1
/DX_N: J1.7, R7.2
/DX_P: J1.1, R6.2
/PULLUP: J1.4, R1.2
/TERM_DN: J1.9, R3.2
/TERM_DP: J1.3, R2.2
/USB_DN: D2.1 (I/O), J2.A7 (D-), J2.B7 (D-), R3.1, R7.1
/USB_DP: D1.1 (I/O), J1.2, J2.A6 (D+), J2.B6 (D+), R1.1, R2.1, R6.1
/VBUS: C5.1, J2.A4 (VBUS), J2.A9 (VBUS), J2.B4 (VBUS), J2.B9 (VBUS), R12.1
/VBUS_DET: J1.10, R12.2, R13.1
/VREF: C1.1, J1.8, R8.2, R9.1
GND: C1.2, C3.2, C4.2, C5.2, D1.2 (GND), D2.2 (GND), J1.5, J1.11, J2.A1 (GND), J2.A12 (GND), J2.B1 (GND), J2.B12 (GND), J2.SH (SHIELD), R9.2, R10.2, R11.2, R13.2

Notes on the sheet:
Pmod USB HS Single: USB 2.0 HS device on one Pmod (Gowin SoftPHY Single LVDS wiring without the D- comparator).
FPGA side: rtl/usb/gowin/usb_phy_gowin_sl.v with CMP1=1 (eda/pmod_usb_hs/SINGLE_PMOD.md). Arora-V (GW5A) values from TN710.
Pmod 1/7 DX_P/DX_N: LVCMOS33D bidirectional pair (transmit + differential receive), R6/R7 in series.
Pmod 2/8 D+ / VREF: LVDS25 input pair = D+ comparator (squelch). VREF = 3.3 V x 200 / 4900 = 135 mV.
Pmod 3/9 TERM_DP/DN: drive low = 45 ohm HS termination (pin + R2/R3), Hi-Z = FS line state input (LVCMOS33).
Pmod 4 PULLUP: high = 1.5k on D+ (FS attach). Pmod 10 VBUS_DET: VBUS / 1.67 (LVCMOS33 input).
UFP only: Rd 5.1k on CC1/CC2, VBUS is not used as a supply. Shield to GND.

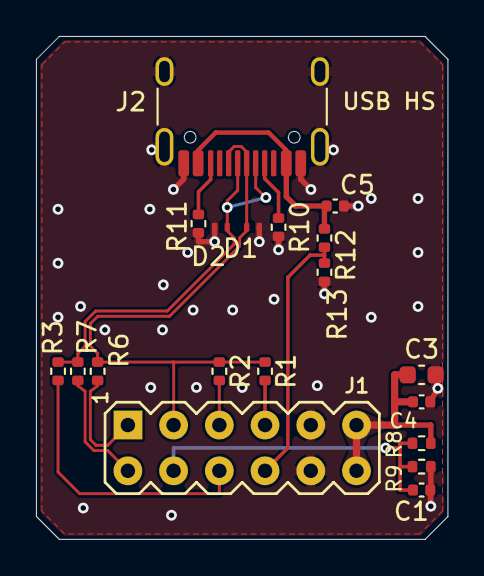
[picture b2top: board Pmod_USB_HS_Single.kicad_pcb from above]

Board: 2 copper layers, 22.9 x 27.9 mm, 20 parts (1 on the bottom side), 14 nets.

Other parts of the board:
LOGO1: Logo_Open_Hardware_Small; logo

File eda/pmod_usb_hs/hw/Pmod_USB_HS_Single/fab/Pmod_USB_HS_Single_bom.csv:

"Reference","Value","Footprint","QUANTITY","LCSC","MPN","Description"
"C1,C5","1u","Capacitor_SMD:C_0402_1005Metric","2","C52923","Samsung CL05A105KA5NQNC","1 uF 10 V X5R 0402 (VBUS),1 uF 10 V X5R 0402 (VREF)"
"C3","10u","Capacitor_SMD:C_0603_1608Metric","1","C19702","Samsung CL10A106KP8NNNC","10 uF 10 V X5R 0603"
"C4","100n","Capacitor_SMD:C_0402_1005Metric","1","C307331","Samsung CL05B104KB54PNC","100 nF 16 V X7R 0402"
"D1,D2","TPD1E05U06DPY","Package_SON:Texas_DPY0002A_0.6x1mm_P0.65mm","2","C436349","TI TPD1E05U06DPYR","1-channel ESD protection, 0.42 pF, X1SON-2"
"J1","Pmod (host)","local:Conn_Pmod_Spec_B_Thin","1","","","Pmod 2x6 right angle (Digilent Pmod Type 1A / spec B)"
"J2","USB_C_Receptacle_USB2.0_16P","Connector_USB:USB_C_Receptacle_HRO_TYPE-C-31-M-12","1","C165948","HRO TYPE-C-31-M-12","USB Type-C receptacle, USB 2.0 (16 pin)"
"R1","1.5k","Resistor_SMD:R_0402_1005Metric","1","C25867","UNI-ROYAL 0402WGF1501TCE","1.5k 1% 0402 (D+ pull-up, soft connect)"
"R2,R3","33","Resistor_SMD:R_0402_1005Metric","2","C25105","UNI-ROYAL 0402WGF330JTCE","33R 1% 0402 (HS termination, D+),33R 1% 0402 (HS termination, D-)"
"R6,R7","100","Resistor_SMD:R_0402_1005Metric","2","C25076","UNI-ROYAL 0402WGF1000TCE","100R 1% 0402 (dx series, D+),100R 1% 0402 (dx series, D-)"
"R8","4.7k","Resistor_SMD:R_0402_1005Metric","1","C25900","UNI-ROYAL 0402WGF4701TCE","4.7k 1% 0402 (VREF ~135 mV)"
"R9","200","Resistor_SMD:R_0402_1005Metric","1","C25087","UNI-ROYAL 0402WGF2000TCE","200R 1% 0402 (VREF)"
"R10,R11","5.1k","Resistor_SMD:R_0402_1005Metric","2","C25905","UNI-ROYAL 0402WGF5101TCE","5.1k 1% 0402 (CC1 Rd),5.1k 1% 0402 (CC2 Rd)"
"R12","100k","Resistor_SMD:R_0402_1005Metric","1","C25741","UNI-ROYAL 0402WGF1003TCE","100k 1% 0402 (VBUS divider, 5 V -> 3.0 V)"
"R13","150k","Resistor_SMD:R_0402_1005Metric","1","C25755","UNI-ROYAL 0402WGF1503TCE","150k 1% 0402 (VBUS divider)"

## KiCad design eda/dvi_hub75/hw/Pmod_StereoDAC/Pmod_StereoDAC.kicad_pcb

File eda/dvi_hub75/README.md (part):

# dvi_hub75 — DVI / HDMI 入力 (720p60) → HUB75 LED マトリクス

Tang Primer 25K で受信した 720p60 の左上 `W × H` 画素を、そのまま (等倍で) 64x64 HUB75 パネルに表示する。
パネル構成は 64x64 / 128x64 / 64x128 / 128x128 (`make PANEL=<W>x<H>`、既定 128x128)。
HDMI の音声 (2ch LPCM) も受けて、1 bit ΔΣ DAC で GPIO 2 本から出す (`rtl/hdmi_rx`)。

```
HDMI/DVI source ─► pmod0 (Pmod DVI) ─► dvi_in_phy (pclk 74.25 MHz, eda/dvi_capture と共通)
   DDC / HPD  ◄─► 40 ピンヘッダ (F1 / F2 / A1)             │ RGB24 / DE / VSYNC     │ データアイランド
                                           rgb_range_expand (AVI)       hdmi_packet_rx → hdmi_audio_rx
                                                           │              → delta_sigma_dac ×2 → D1 / E3 → RC LPF
                                    crop_to_hub75: 左上 W×H を切り出し、チェーン上のアドレスへ
                                                           │ {flip, addr, RGB555}
                                                async FIFO (pclk → 50 MHz)
                                                           ▼
                                    Hub75 (rtl/hub75): ダブルバッファ VRAM、6 bit BCM
                                                           ▼
                                pmod1 + pmod2 (HUB75 Pmod ベースボード) ─► パネル
```

## ビルドの変種

| 変数 | 値 | 内容 |
|---|---|---|
| `PANEL` | `64x64` / `128x64` / `64x128` / `128x128` (既定) | 表示サイズ |
| `BITS` | `5` / `6` (既定) | 色あたりの BCM ビットプレーン数 |
| `HUB75_CLKDIV` | `0` (既定) / `1` | HUB75 のシフトクロック分周。CLK = 50 MHz / (2 × (N + 1) + `HUB75_CLKLOW`)、`HUB75_CLKDIV=1 HUB75_CLKLOW=0` で 12.5 MHz |
| `GAMMA` | 例 `2.2` (既定は恒等) | 色テーブルの初期値 (リセット後と `i`) をガンマ `<g>` にする (`gen_lut_init.py`、表示ビット数で丸め)。UART なしで動かす展示用 |
| `HDMI_AUDIO` | `1` (既定) / `0` | 1: HDMI 用 EDID (CEA-861 拡張、2ch LPCM) で音声を受ける。0: DVI 専用 EDID (音声なし、レンジ変換なし) |
| `HUB75_CLKLOW` | `0` / `1` (既定) | 1 画素あたり CLK Low を延ばすティック数。既定の組み合わせで 16.7 MHz (Low 40 ns / High 20 ns) |

128x128 の比較 (リフレッシュはシミュレーションで測った 1 走査の長さ、合成は Gowin 1.9.12):

| 構成 | リフレッシュ | BSRAM | タイミング |
|---|---|---|---|
| 5 bit、12.5 MHz (`BITS=5 HUB75_CLKDIV=1 HUB75_CLKLOW=0`) | 254 Hz | 37/56 | 違反なし |
| 6 bit、12.5 MHz (`HUB75_CLKDIV=1 HUB75_CLKLOW=0`) | 190 Hz | 41/56 | 違反なし |
| 6 bit、16.7 MHz (既定) | 234 Hz | 41/56 | 違反なし (実機で正常) |
| 6 bit、25 MHz (`HUB75_CLKLOW=0`) | 305 Hz | 41/56 | 違反なし (実機では B2 を取りこぼす) |

ホスト側のガンマテーブルは表示ビット数で丸める (`loopctl.py gamma 2.2` は既定で 6 bit、5 bit 版では `loopctl.py gamma 2.2 rgb 5`)。
25 MHz のシフトクロックは実機 (64x64 × 4 枚のチェーン) では通らなかった。上段パネルの行 32–63 で B2 が
まったく出ず (黄色っぽく見える)、12.5 MHz に戻すと正常に表示された (2026-10-01)。
チェーンの途中で B2 の波形がなまって、それより先のパネルで取りこぼしていると見られる。
遠い側のパネルのデータは上流パネルのドライバ IC が CLK に合わせて出し直したものなので、FPGA 側の
ドライブ能力や出力遅延では直らず、CLK の周期を延ばすしかない。1 画素を Low 2 + High 1 クロックにした
16.7 MHz (`HUB75_CLKLOW=1`) では正常に表示された (234 Hz)。Low 側を延ばすのは、上流のドライバが CLK の
立ち下がりで出力を変える品種でも次の立ち上がりまでの時間を稼げるようにするため。

## パネルの配置

64x64 パネル (1/32 スキャン、A〜E) は、パネル内の行 0–31 が R1G1B1、行 32–63 が R2G2B2 (同じ行アドレス)。
高さ 128 の構成は電気的には 1 本のチェーンで、下半分 (y 64–127) の 64 行が上半分の右側につながる
(128x128 = 256x64)。表示座標 (x, y) → VRAM アドレス:

```
seg     = y / 64            下半分なら 1
yy      = y % 64
half    = yy / 32           0: R1G1B1, 1: R2G2B2
scan    = yy % 32           行アドレス A..E
chain_x = seg * W + x       (CHAIN_REVERSE パラメータで反転)
addr    = {half, scan, chain_x}
```

チェーン上の向き (最初にシフトした画素が左端に来るか右端に来るか) は実機で確認する。左右が逆なら
`crop_to_hub75` の `CHAIN_REVERSE` を 1 にする。

## バッファの方式

1 フレーム分のフレームバッファ (ダブルバッファ) を持つ。HUB75 は BCM のビットプレーンごとに同じ行を送り直しながら
入力と無関係に数百 Hz で走査し続けるうえ、1 回のシフトに表示行 r / r+32 / r+64 / r+96 が同時に要るので、
上半分だけを FIFO に溜める方式では足りない (待ち量がほぼ 1 フレームになる)。

- 128x128 × RGB555 × 2 面 = BSRAM 32 個 (全体で 35/56)。64x64 は 11/56
- 書き込みは切り出し範囲の最終行のあとに FLIP を送り、表示側はパネルのフレーム境界で面を切り替える (ティアリングなし)
- 前回の FLIP がまだ消化されていないうちに次のフレームが来たら、そのフレームは書かずに捨てる

## 階調 (6 bit BCM)

パネルの LED は点灯 / 消灯しかできないので、`rtl/hub75` が BCM (Binary Code Modulation) で明るさを作る。
色ごとの 6 bit 値をビットプレーンに分け、各行について MSB → LSB の順に「そのビットが 1 の画素だけ点灯」を
重み付きの時間だけ表示する (64³ = 262,144 色)。

| ビット | 重み | 点灯時間 (OE、50 MHz) |
|---|---|---|
| bit5 (MSB) | 32 | 1024 クロック (20.5 µs) |
| bit4 | 16 | 512 (10.2 µs) |
| bit3 | 8 | 256 (5.1 µs) |
| bit2 | 4 | 128 (2.6 µs) |
| bit1 | 2 | 64 (1.3 µs) |
| bit0 (LSB) | 1 | 32 (0.64 µs) = 2 × `BASE_OE_CYCLES` |

例えば値 45 (101101b) は 1024 + 256 + 128 + 32 = 1440 クロック点灯し、全点灯 (2016) の 45/63 の明るさになる。
PWM なら行ごとに 64 区切りが要るところを、同じ行のデータを 6 回送り直すだけで済む。

1 行の手順は、ビットプレーンごとに「256 画素 (4 枚のチェーン) をシフト (16.7 MHz で 768 クロック、15.4 µs) →
LAT でラッチ → OE を重みの時間だけ有効」を 6 回。点灯中は CLK / LAT を動かさない (シフトと点灯は重ならない)。
1 行約 6650 クロック (133 µs) × 32 行 (1/32 スキャン) = 約 212,800 クロック = 4.26 ms で、これが 234 Hz の内訳。

- ビットを増やすとシフトが 1 回増え、MSB の点灯時間も倍になるので更新レートが下がる。LSB を 0.32 µs まで
  短くするとドライバや LED の応答が追いつかず、暗部が値どおりにならない (階調のつぶれ・ゴースト)
- ガンマ 2.2 では暗い側の段階が粗くなる (6 bit で入力 29 未満、5 bit で 40 未満が消灯)。6 bit にしたのはこのため
- 1 行の時間のうち点灯は約 30% (2016 / 約 6650)、さらに 32 行で時分割するので、LED 1 個の最大点灯率は約 1%。
  明るさが要るなら、前の行の点灯中に次のデータをシフトする (CLK / LAT の規則を緩める) か、`BASE_OE_CYCLES` を
  大きくする (更新レートが下がる)

## 色テーブル (ガンマ補正 / ホワイトバランス)

`crop_to_hub75` は R / G / B それぞれに 256 エントリ × 8 bit のテーブルを持ち、入力の 8 bit 値で引いた結果の
上位 `COMPONENT_BITS` (6) bit を表示する。デュアルクロック BSRAM (書き込みは 50 MHz、読み出しはピクセルクロック)。

- 既定 (リセット後) は恒等 = ガンマ 1.0 (入力の上位ビットをそのまま表示、テーブルなしと同じ)
- UART から更新: `G<mask><512 桁の 16 進>` (mask = bit0 R / bit1 G / bit2 B、256 バイトをエントリ 0 から)、
  `i` で恒等に戻す。行の出力中でも取りこぼさない
- ホスト: `loopctl.py gamma 2.2` (全チャネル)、`loopctl.py gamma 2.0 r` (R だけ)、`loopctl.py gamma identity`。
  値は `round((in/255)^g × 63) << 2` (6 bit 表示に合わせて丸めた 8 bit 値)
- ガンマ 2.2 にすると、6 bit 表示では入力 29 未満、5 bit 表示では入力 40 未満が 0 になる

## ピン

| 信号 | ピン |
|---|---|
| DVI RX | pmod0 (H5 / H8 / G7 / F5、LVDS25 + 内蔵終端 + CTLE HIGH) |
| DDC SCL / SDA / HPD | 40 ピンヘッダ 15 (F1) / 16 (F2) / 17 (A1)。18 (E1) は CEC 用に予約。11 = +5V、12 = GND |
| HUB75 | pmod1 + pmod2 (`pins.cst`)。ベースボードのモジュール側 pmod0 (RGB / E / B) が pmod2 (G11 側)、pmod1 (LAT / CLK / OE / A / C / D) が pmod1 (A11 側) |
| UART | C3 (TX) / B3 (RX)、115200 8N1 |
| 状態出力 | B2 = ワードロック、C2 = デコードエラー (40 ピンヘッダ 14 / 13) |
| S1 (H10) | HPD を 200 ms 下げて EDID を読み直させる |
| 音声 DAC L / R | 40 ピンヘッダ 19 (D1) / 20 (E3)、LVCMOS33 DRIVE=8 |

DDC はソース側で 5 V にプルアップされるので、レベル変換 (PCA9306 等) かクランプを入れる。

## 音声

`HDMI_AUDIO=1` (既定) では EDID に CEA-861 拡張 (2ch LPCM 32 / 44.1 / 48 kHz、HDMI VSDB、RGB レンジ選択可) を
載せるので、ソースは HDMI で送り、データアイランドに音声を載せる。再生レートは ACR の N / CTS から
fs = f_TMDS × N / (128 × CTS) で再現する (詳細は `rtl/hdmi_rx/README.md`)。

- ΔΣ DAC は 2 次 1 bit、更新は 74.25 MHz / 12 = 6.1875 MHz。数値モデルとシミュレーションでの帯域内
  (20 Hz–20 kHz) SNR は 88 dB (フルスケール正弦波)。実際はピンの電源ノイズとエッジの非対称で決まる
- AVI InfoFrame がリミテッドレンジ (Q = 1、または Q = 0 で CE フォーマット) なら RGB をフルレンジに伸ばしてから
  色テーブルに入れる。VCDB で QS = 1 を宣言しているので、多くのソースはフルレンジで送る
- 実機 (ノート PC、2026-10-01): HDMI として認識、N = 11648 / CTS = 140625 (fs = 48000.4 Hz)、パケットの
  パリティ誤り 0、FIFO のアンダーラン / オーバーランなし、フルレンジ

### LPF (チャネルごと)

```
D1 / E3 ─ R1 1kΩ ─┬─ R2 10kΩ ─┬─ C3 1µF ─→ 出力 (入力インピーダンス 47kΩ 以上のアンプ / ライン入力)
                  C1 3.3nF     C2 330pF
                  │            │
                 GND          GND
```

- 1 段目・2 段目ともカットオフ約 48 kHz。2 段目の R を 1 段目の 10 倍にして段間の干渉を減らす
- 周波数特性 (ピンの出力インピーダンス 30 Ω 込みの計算): −3 dB が 28.5 kHz、20 kHz で −1.6 dB、100 kHz で −15 dB、
  1 MHz で −53 dB、6.19 MHz で −85 dB
- 20 kHz まで平坦にするなら C1 = 2.2 nF、C2 = 220 pF (−3 dB 約 43 kHz、20 kHz で −0.7 dB、6.19 MHz で約 −77 dB)
- C3 は直流カット (出力の中心は 1.65 V)。47 kΩ 負荷で低域 −3 dB は 3.4 Hz
- フルスケール正弦波で約 1.1 Vrms (ラインレベル相当)。出力インピーダンスが約 10 kΩ なのでヘッドホンは直接駆動できない
- さらに良くするなら、静かな電源の 74LVC1G74 などでピンの出力を打ち直してから LPF に入れる (I/O 電源のノイズが
  そのまま出力に乗るため)

## UART

`eda/dvi_capture` と同じ診断 (`eda/dvi_loopback/host/loopctl.py`)。X = {DDC SCL 立ち下がり回数 (14), SCL, SDA, EDID 読み出しバイト数 (16)}、
Y = {HPD (1), FIFO オーバーフロー回数 (15), 捨てたフレーム数 (8), DDC オフセット (8)}。
Z0 = {パケット数 (16), ヘッダのパリティ誤り (8), サブパケットのパリティ誤り (8)}、
Z1 = {N (20), 音声 FIFO の水位 / 2 (9), リミテッドレンジ, 再生中, TERC4 異常あり}、
Z2 = {CTS (20), アンダーラン (6), オーバーラン (6)}。`loopctl.py audio` で解読して fs も出す。

## シミュレーション

`make sim` (`test/`): 映像源 → `crop_to_hub75` → async FIFO → `Hub75` → HUB75 パネルモデル。パネルモデルは
CLK 立ち上がりでシフト、LAT でラッチ、OE が Low の間 (ビット × 期間) を行アドレスの画素に積算し、
1 回の走査で表示される値を全画素について期待値と比べる。パネル構成・ビット数・シフトクロックの 8 構成それぞれで、
2 つの絵を順に表示して全画素一致 (途中で混ざらない) を確認する。
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
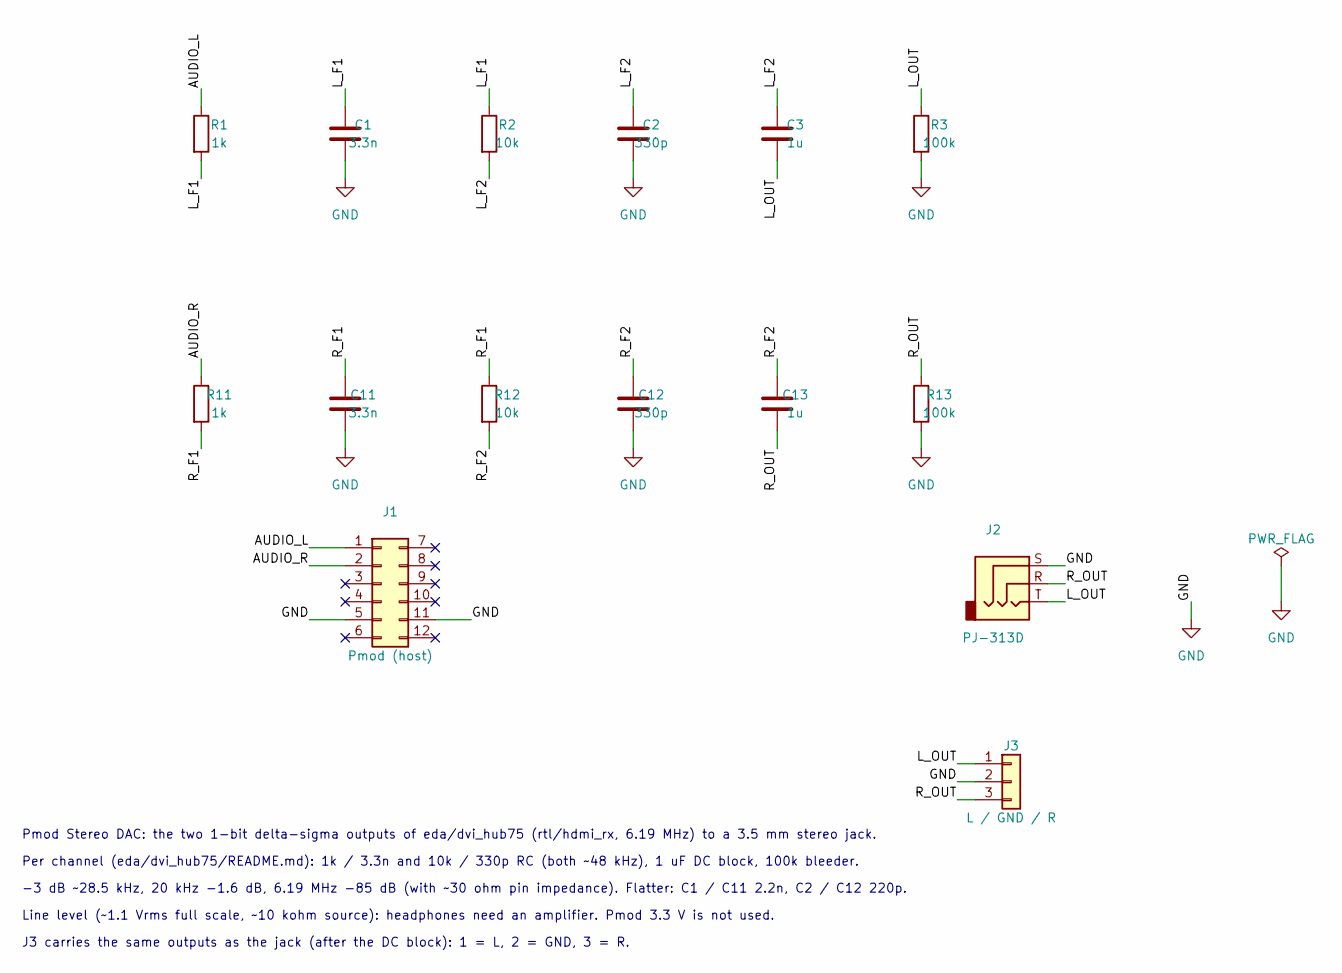
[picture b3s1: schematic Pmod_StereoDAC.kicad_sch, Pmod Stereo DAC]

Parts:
C1, C11: 3.3n; C_0603_1608Metric; MPN YAGEO CC0603JRNPO9BN332; LCSC C107048
C2, C12: 330p; C_0603_1608Metric; MPN Samsung CL10C331JB8NNNC; LCSC C1664
C3, C13: 1u; C_0805_2012Metric; MPN Samsung CL21B105KBFNNNE; LCSC C28323
J1: Pmod (host); Conn_Pmod_Spec_B_Thin; MPN 2x6 2.54 mm right-angle pin header (han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
J2: PJ-313D; Jack_3.5mm_SHOUHAN_PJ-313D_Horizontal; MPN SHOU HAN PJ-313D; LCSC C668608
J3: L / GND / R; PinHeader_1x03_P2.54mm_Vertical; MPN BOOMELE 2.54-1*3P; LCSC C49257
R1, R11: 1k; R_0603_1608Metric; MPN UNI-ROYAL 0603WAF1001T5E; LCSC C21190
R2, R12: 10k; R_0603_1608Metric; MPN UNI-ROYAL 0603WAF1002T5E; LCSC C25804
R3, R13: 100k; R_0603_1608Metric; MPN UNI-ROYAL 0603WAF1003T5E; LCSC C25803

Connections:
/AUDIO_L: J1.1, R1.1
/AUDIO_R: J1.2, R11.1
/L_F1: C1.1, R1.2, R2.1
/L_F2: C2.1, C3.1, R2.2
/L_OUT: C3.2, J2.T, J3.1, R3.1
/R_F1: C11.1, R11.2, R12.1
/R_F2: C12.1, C13.1, R12.2
/R_OUT: C13.2, J2.R, J3.3, R13.1
GND: C1.2, C2.2, C11.2, C12.2, J1.5, J1.11, J2.S, J3.2, R3.2, R13.2

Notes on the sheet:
Pmod Stereo DAC: the two 1-bit delta-sigma outputs of eda/dvi_hub75 (rtl/hdmi_rx, 6.19 MHz) to a 3.5 mm stereo jack.
Per channel (eda/dvi_hub75/README.md): 1k / 3.3n and 10k / 330p RC (both ~48 kHz), 1 uF DC block, 100k bleeder.
-3 dB ~28.5 kHz, 20 kHz -1.6 dB, 6.19 MHz -85 dB (with ~30 ohm pin impedance). Flatter: C1 / C11 2.2n, C2 / C12 220p.
Line level (~1.1 Vrms full scale, ~10 kohm source): headphones need an amplifier. Pmod 3.3 V is not used.
J3 carries the same outputs as the jack (after the DC block): 1 = L, 2 = GND, 3 = R.

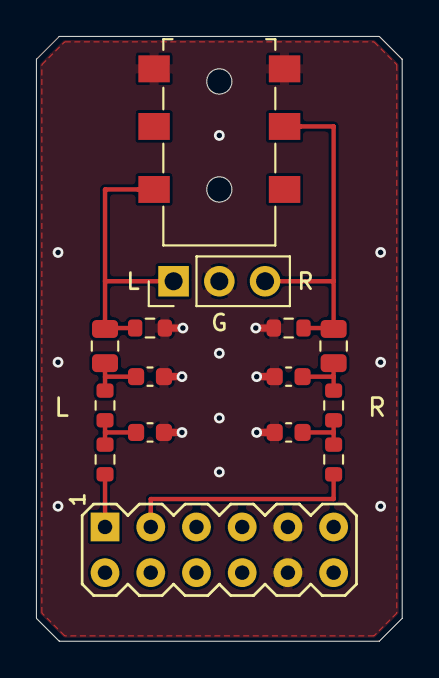
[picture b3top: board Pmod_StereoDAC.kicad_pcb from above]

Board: 2 copper layers, 20.3 x 33.6 mm, 16 parts (1 on the bottom side), 9 nets.

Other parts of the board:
LOGO1: logo

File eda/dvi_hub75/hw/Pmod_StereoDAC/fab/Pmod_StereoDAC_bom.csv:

"Reference","Value","Footprint","QUANTITY","LCSC","MPN","Description"
"C1,C11","3.3n","Capacitor_SMD:C_0603_1608Metric","2","C107048","YAGEO CC0603JRNPO9BN332","3.3 nF 50 V C0G 5% 0603"
"C2,C12","330p","Capacitor_SMD:C_0603_1608Metric","2","C1664","Samsung CL10C331JB8NNNC","330 pF 50 V C0G 5% 0603"
"C3,C13","1u","Capacitor_SMD:C_0805_2012Metric","2","C28323","Samsung CL21B105KBFNNNE","1 uF 50 V X7R 10% 0805 (DC block)"
"J1","Pmod (host)","local:Conn_Pmod_Spec_B_Thin","1","","2x6 2.54 mm right-angle pin header (hand soldered)","Pmod 2x6 right angle (Digilent Pmod Type 1A / spec B)"
"J2","PJ-313D","local:Jack_3.5mm_SHOUHAN_PJ-313D_Horizontal","1","C668608","SHOU HAN PJ-313D","3.5 mm stereo jack, SMD (SHOU HAN PJ-313D): tip = L, ring = R, sleeve = GND"
"J3","L / GND / R","Connector_PinHeader_2.54mm:PinHeader_1x03_P2.54mm_Vertical","1","C49257","BOOMELE 2.54-1*3P","1x03 2.54 mm pin header, vertical: 1 = L, 2 = GND, 3 = R (line out, after the DC block)"
"R1,R11","1k","Resistor_SMD:R_0603_1608Metric","2","C21190","UNI-ROYAL 0603WAF1001T5E","1 kOhm 1% 0603"
"R2,R12","10k","Resistor_SMD:R_0603_1608Metric","2","C25804","UNI-ROYAL 0603WAF1002T5E","10 kOhm 1% 0603"
"R3,R13","100k","Resistor_SMD:R_0603_1608Metric","2","C25803","UNI-ROYAL 0603WAF1003T5E","100 kOhm 1% 0603"
